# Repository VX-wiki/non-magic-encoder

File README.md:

# Non-Magic Encoder

> ### ⚠️ Read this first: do you actually need one?
>
> **The stock Broadcom optical encoder is magically good when it works.** It is accurate, clean, and there is genuinely nothing wrong with it. Its *only* real weakness is that it is **mechanically fragile**: a delicate optical disc, optics, and aging plastic living in a hot, vibrating drivetrain. If your optical encoder is healthy, **leave it alone**. Nothing here will beat it.
>
> **Non-Magic has no magical properties.** Per the comparison report it does an essentially **identical job**: same current per torque, same heat, same efficiency. It will **not** make your scooter faster, more efficient, or smoother. Treat any apparent "improvement" as noise until proven otherwise.
>
> **This is still hardware under active test.** Non-Magic R1 is community beta with limited hours on a single bike. A lot can still go wrong: installation, adhesives, alignment, calibration, and long-term durability are all unproven at scale. The *one* thing it is meant to bring, better mechanical robustness from having no fragile optical disc, is **plausible but unproven**, and only earns that title after years of real-world service. The only honest reason to fit one today is that your optical encoder has already failed, or you are deliberately experimenting and accept the risk.

## Status and scope

Non-Magic R1 is **community-beta DIY hardware that is still actively under test.**

It has been bench-tested and road-tested on the author's single Vectrix VX-1 and, in those limited conditions, has shown no measurable power, efficiency, current, or heat penalty versus the OEM optical encoder. That is the *whole* of the evidence so far: one bike, a modest number of hours, one rider. It is a small-batch maker project, not a mass-produced, durability-qualified, or independently certified vehicle component.

**Expect problems.** Installation, calibration, adhesives, alignment, and long-term durability are all places where it can and may go wrong. The headline claim of better *mechanical robustness* over the optical encoder is plausible but **not yet proven**. It only earns that title after surviving years of heat, vibration, and moisture in service. Until then, assume Non-Magic is, at best, an *equal* to a working optical encoder, with robustness as an unproven bet.

Use it only if you understand the installation, calibration, and testing procedure, and only if you are comfortable being part of that test.

## What is this?

Non-Magic is a calibrated magnetic replacement encoder for the Vectrix VX-1 motor: a practical, mechanically robust drop-in for when the fragile stock optical encoder finally fails.

**Why "Non-Magic"?** There is a lot of magic out there: black-box encoders locked to one motor controller, with proprietary firmware you cannot read, repair, or replace. This is a *non-magical* encoder. It is open hardware you can modify, build, and experiment with as you please.

**Works with any stock motor controller firmware.** Non-Magic fully emulates the original optical encoder's parameters, with line-driver outputs matched to the original. There is nothing to reflash on the controller and no firmware lock-in. It drops in and behaves like the factory encoder. The goal is to **match** the optical encoder from a more mechanically robust platform, not to beat it.

A good encoder matters because the motor controller has to know rotor position before it can switch the windings cleanly. A weak or misaligned encoder can still make the wheel turn, but it can also add current ripple, heat, whine, rough commutation, lower efficiency, and extra stress on the inverter capacitors. The encoder is a small part, but it decides how cleanly the whole motor system works.

The comparison report now covers **two tests**, both against the factory optical encoder on the same stock controller firmware:

- **Bench (no-load).** On the stand, Non-Magic held its own on power and produced a slightly cleaner commutation signature through the main test band, with more sharply defined motor switching, run for run.
- **Road (loaded).** Ridden on public road under real load up to ~110 A, the two encoders were **indistinguishable**: same current for the same torque (within ~1%), the same heat in the inverter and DC-link capacitors, the same cruise/touring consumption (whole-ride energy 689 vs 690 Wh), and the same regen behaviour. The road test closes the bench's main open question: loaded efficiency and component heating.

The honest bottom line: across both tests the calibrated Non-Magic encoder performs **at least as well** as the OEM optical encoder, with no measurable power, efficiency, or heat penalty. "At least as well" is the ceiling of the claim, not a promise of better, and it still rests on a single bike over limited hours. Read the full comparison report here:

[Non-Magic encoder comparison report (rev2: bench + road)](assets/docs/Non-Magic-encoder-comparison-report-rev2-270626.pdf)

## Specifications

| | |
| --- | --- |
| Sensing IC | MT6835, 21-bit high-accuracy magnetic angle encoder |
| Core resolution | 21-bit |
| Accuracy | User auto-calibration with distortion compensation, target INL < ±0.07° |
| Max rotation speed | Up to 120,000 RPM |
| Operating temperature | −40 to +125 °C |
| Output drivers | AM26C31QDR automotive line drivers |
| Output interface | Connections match the original optical encoder |
| Controller firmware | Works with any stock motor controller firmware. Fully emulates the original encoder's parameters, no reflash, no lock-in |
| Mounting | Robust mechanical mount, designed for a hot, vibrating drivetrain |

## Buy DIY Kit

<p align="center">
  
  <br>
  <sub>self installation required · community-beta, install at your own risk</sub>
</p>

<p align="center">
  <strong>Proceeds support a non-profit makerspace in Riga, Latvia.</strong><br>
  <sub>The first R1 batch is personally funded by the maintainer; Stripe proceeds after payment processing fees go to the makerspace.</sub>
</p>

> ⚠️ **DIY community-beta kit: read before buying or building.**
>
> This is a limited R1 DIY repair/experimenter kit for experienced Vectrix VX-1 owners. It is **not** a plug-and-play consumer accessory: not type-approved, not independently safety-certified, and not supplied as a certified road-use safety component.
>
> Installation requires correct mechanical fitment, magnet alignment, adhesive use, wiring, encoder self-calibration, and motor-controller offset calibration. Incorrect installation or calibration can cause rough commutation, loss of propulsion, overheating, motor or controller damage, or unsafe vehicle behaviour.
>
> Buy only if you can install, inspect, calibrate, and test it yourself. Start with the wheel lifted, test gently, and stop using it immediately if you hear abnormal noise, feel rough running, see faults, or notice unusual heat.
>
> Nothing here limits any mandatory rights or remedies that cannot legally be excluded.

Every board is **tested, programmed, and conformal coated** before it ships. The kit includes **all required parts except threadlocker and adhesive** (listed as consumables below).

## PCB

## How to Install and Use

> ⚠️ **Safety first: read before you touch anything.**
>
> - **Always on the centre stand.** Every calibration and test step below is done with the bike on its centre stand and the **driven (rear) wheel off the ground and free to spin**. The motor can spin that wheel on its own during offset calibration, so never do this with the wheel able to drive the bike.
> - **High voltage.** The Vectrix runs on high-voltage traction electronics. Treat the battery, controller, and wiring as live and dangerous at all times, and take every sane high-voltage precaution whenever you work on the bike.

Installation walkthrough video:

https://github.com/user-attachments/assets/6c1a84cd-9490-44e6-9311-1ca9467ff3d4

A key advantage of Non-Magic is that it **self-calibrates once installed**. The on-board MT6835 builds its own angle-error correction map while the rotor turns slowly. You just spin the rear wheel at roughly 5 km/h with a hand drill pressed against the tyre and hold the calibration button. No special rig, no PC required for this step.

### 1. Mechanical installation

1. **Remove the original encoder assembly.**
2. **Clean the area thoroughly.** No dust, grease, oil, or other contaminants may remain in the motor encoder cavity. A clean, dry surface is critical for both the adhesive bond and the magnetic reading.
3. **Install the magnet holder.** Apply adhesive and push the magnet holder on until the motor shaft bottoms out inside it. Watch the slot in the shaft and the magnet holder; they must align cleanly. Allow the adhesive to set if possible.
4. **Attach the encoder assembly to the motor case.** Use threadlocker on the bolts. Fit each bolt with a wide washer and a serrated washer. **Do not overtighten.**
5. **Connect the encoder connector.**

There are **two separate calibrations**, and they must not be confused:

- **Encoder ASIC self-calibration** (Section 2) calibrates the **encoder**. It runs on the encoder's own MT6835 chip and corrects the magnetic sensor's per-revolution angle-error map, using the **encoder's calibration button and LED**.
- **Motor offset calibration** (Section 3) calibrates the **inverter**. It runs on the Vectrix motor controller, either in diagnostic software or via the throttle/brake/ignition "combo", and teaches the controller the fixed angle between encoder zero and the rotor's magnetic zero.

Do both, in this order. They are different procedures on different hardware; the encoder button does not trigger the controller offset cal, and the controller combo does not trigger the ASIC self-cal.

### 2. Encoder ASIC self-calibration (on the encoder)

1. **Power on the bike, but do not try to start it.**
2. **Turn the wheel by hand and watch the LED.** It should give **5 pulses per wheel revolution**. If it does, the magnet and alignment are good.
3. **Run the calibration spin.** Put the bike on the centre stand and spin the rear wheel with a hand drill pressed against the tyre, holding roughly **5 km/h** (read off the dash or scooter diagnostic software).
4. **Hold the calibration button.** Calibration needs **more than 64 rotations** to complete; expect to hold the button for under ~20 seconds. **THE SPEED TARGET IS APPROX 10-30-ish km/h, so no need to be very precise. If you are too slow or fast- it will just fail and let you know with the led** The LED shows progress:

   | LED state | Meaning |
   | --- | --- |
   | Half brightness | Calibration in progress |
   | Dim | Calibration failed |
   | Full on | Calibration succeeded |

5. **Turn the bike fully off** once calibration succeeds.

### 3. Motor offset calibration (on the inverter)

After the on-board self-cal, the motor controller still needs its own encoder-offset calibration.

**With the Vectrix diagnostics software:** turn the bike on and run the encoder calibration from the diagnostic application. Note this needs a **PeakCAN cable** to talk to the controller. If you don't have one, you can't use the software, so use the combo procedure below instead.

**Without software, the built-in combo procedure:** the controller has a hidden calibration mode you trigger straight from the bars, no cable or software required. (This is the same throttle/brake/ignition combo Vectrix documented for the original optical encoder; it works identically here.)

1. Put the bike on its **centre stand** and confirm the rear wheel is off the ground, free to spin, and the bike is stable.
2. Fold up the side-stand / kickstand.
3. Make sure the ignition key is in the **OFF** position.
4. Press the kill switch to the **RUN** position.
5. Turn the throttle **fully open** and squeeze the **left brake** lever, and hold both.
6. While still holding throttle and brake, turn the ignition **ON**.
7. Keep holding until the dashboard activates and the **WRENCH** icon / tell-tale light stays on, then release the throttle and brake.
8. Calibration starts automatically: the wheel begins to rotate and the speedometer needle sweeps from 0 km/h up to 120 km/h and back to zero.
9. After a few seconds the **WRENCH** icon disappears. Calibration is done.
10. If the process repeats itself over and over, the encoder cannot find a valid calibration; it requires inspection, cleaning, or replacement.

> **Caution:** the bike is still in GO mode during and after this procedure. Turning the throttle will activate the motor.

Then test gently first, listening for rough commutation or abnormal motor/controller heat.

> **Note: check your phase wiring.** The author's bike came equipped with a "magic" commercial magnetic encoder as purchased, and its motor phase wires were connected A-B, B-C, C-A. Neither the optical nor the magnetic encoder would work until the phases were swapped back to their respective factory positions: A-A, B-B, C-C. If the motor refuses to run or commutates badly regardless of encoder calibration, verify the phase wiring is in its correct factory order before troubleshooting the encoder further.

Installation consumables:

| No | Name | Qty | Notes | Link |
| ---: | --- | ---: | --- | --- |
| 1 | Threadlocker, blue or red | as needed | For encoder holder to motor case | commodity |
| 2 | Magnet holder to motor adhesive | as needed | Preferred order: automotive gasket maker, toughened cyanoacrylate, two-part epoxy, threadlocker | commodity |

## Make Your Own

Or make your own. The full design sources are below.

> ⚠️ **License first.** These files are released under **CC BY-NC-SA 4.0**. You may build, modify, and share them, but you may **not sell them or profit in any way**, and any derivative must stay under the same license. See [License](#license). No magic, no freeloading.

**Total cost is roughly €25–60 per unit**, depending on how you scale and source the parts and what tools and materials you already have on hand.

The DIN fasteners are standard commodity parts; source them from any supplier by their DIN number.

| No | Name | Image | Qty | Notes | Link |
| ---: | --- | :---: | ---: | --- | --- |
| 1 | Main PCB |  | 1 | Gerbers + assembly files | [production archive](hardware/kicad/production/non-magic-encoder-r1.zip) |
| 2 | Printed PCB holder* |  | 1 | FDM PA6-GF, PA6-CF, PPS-CF, or MFJ PA12-GB. IMPORTANT! | [STL](hardware/printed-parts/encoder-printed-holder-r1.STL) |
| 3 | Printed magnet holder* |  | 1 | FDM PA6-GF, PA6-CF, PPS-CF, or MFJ PA12-GB. IMPORTANT! | [STL](hardware/printed-parts/magnet-holder-r1.STL) |
| 4 | 3M DP8910NS adhesive | | 0.1 g | Bonds the magnet to the printed nylon holder. Alternate adhesive can be used, but it is risky; see note below | [3M](https://www.3m.com/) |
| 5 | 10x5 neodymium magnet |  | 1 | N45 or better, diametrically magnetized | commodity |
| 6 | Sleeve DIN 7340 | | 4 | Cu, 2.6 x 5 x 3 | commodity |
| 7 | Washer DIN 9021 | | 4 | M2.5, OD8 | commodity |
| 8 | Washer DIN 6798 Type A | | 4 | M2.5 | commodity |
| 9 | Bolt DIN 7985 | | 4 | M2.5, length to suit installation | commodity |
| 10 | Screw DIN 7981 ST 2.0 x 6 | | 4 | EJOT PT is better | commodity |
| 11 | Conformal coating | | as needed | Weatherproof the populated PCB; see note below | commodity |

*The encoder lives in a harsh environment. You must use glass-filled high-performance material for the encoder support. PA6-GF is used in the current units. Standard SLS PA12 or PA11 may not be up to the task.

**Why the 3M DP8910NS adhesive matters:** nylon (PA6 through PA12) is a *low surface energy* plastic, so most common adhesives will not key into it and the bond fails. DP8910NS is formulated specifically for low-energy substrates like nylon and polypropylene, which is why it is the recommended choice for bonding the magnet to the printed holder. Substituting a general-purpose adhesive is the most likely way to end up with magnet delamination.

**Conformal coating is important.** The encoder lives in a harsh place: heat, vibration, moisture, and contamination. Conformal coating the populated PCB is essential weatherproofing that protects against corrosion and conductive dirt. Factory-built kits ship already coated; if you build your own, do not skip this step.

### Design files

Everything needed to fabricate, assemble, or modify the board:

| File | Description |
| --- | --- |
| [Schematic (PDF)](hardware/non-magic-encoder-r1-schematic.pdf) | R1 schematic |
| [Production archive (ZIP)](hardware/kicad/production/non-magic-encoder-r1.zip) | Gerbers, BOM, and pick-and-place for fabrication |
| [KiCad project](hardware/kicad/) | Editable sources (`.kicad_pro`, `.kicad_sch`, `.kicad_pcb`), libraries, and footprints |
| [Board STEP model](hardware/encoder-pcb-r1.step) | 3D model of the assembled PCB |
| [PCB holder STL](hardware/printed-parts/encoder-printed-holder-r1.STL) | Printed encoder support (glass-filled material, see note above) |
| [Magnet holder STL](hardware/printed-parts/magnet-holder-r1.STL) | Printed magnet carrier (glass-filled material, see note above) |
| [MT6835 datasheet](hardware/kicad/docs/MT6835_Rev.1.3.pdf) | Sensing IC reference |

## Informal Risk Assessment

A short FMEA-style note on the failure modes that actually matter on this hardware. This is not an ISO 26262 compliance claim, safety case, or certification. Severity, likelihood, and controllability are qualitative.

| Failure mode | Cause | Effect | Severity | Risk reduction |
| --- | --- | --- | --- | --- |
| Bad commutation | Magnet misalignment or skipped auto-calibration | Motor switches at the wrong angle, drawing excess current and overheating the motor and controller | Medium-High | Verify magnet centering and air gap, run the auto-calibration before riding, test first with the wheel lifted and watch for abnormal heat |
| Loss of board power | Cracked or shorted MLCC on the PCB shorts the supply and trips the upstream resettable fuse | Encoder goes dead, controller loses position, **motor coasts to a halt** (no torque, not a runaway) | Medium | Use quality MLCCs, avoid board flex during assembly and mounting, handle the populated PCB carefully |
| Mechanical failure | Magnet delamination: the magnet's adhesive bond to its holder lets go | Position signal is lost or wrong, propulsion drops out | Medium | Use the ranked adhesives with proper surface prep, use only glass-filled holder material, inspect after the first heat cycles |

Before riding: confirm the magnet is centred, run auto-calibration, and do the first run with the driven wheel lifted and a safe way to cut power. Treat any suspected encoder fault as stop-use until inspected. Road or public-use suitability is outside the scope of this project.

## Getting help

Two ways to get help or report a problem:

- **Open an issue.** [Create an issue in this repo](../../issues/new) for bugs, broken links, install trouble, or questions. This is the best place for anything others might hit too.
- **Chat with the community.** Reach out on WhatsApp in the **Open Source Magic Encoder** group, part of the wider **Vectrix Worldwide** community. It's the fastest way to get hands-on install and calibration help from other owners.

## Contributing

Contributions are welcome. Fork the repo, make your changes, and open an issue or pull request:

- **Found a bug or have an idea?** Open an issue first so it can be discussed.
- **Improved the hardware, holders, or docs?** Fork it, commit your changes, and open a pull request from your fork.

Anything you contribute is released under the same **CC BY-NC-SA 4.0** license as the rest of the project (see below), so improvements stay open for everyone.

## License

This project is licensed under the Creative Commons Attribution-NonCommercial-ShareAlike 4.0 International license (CC BY-NC-SA 4.0). See [LICENSE](LICENSE).

In plain terms:

- **Attribution.** You may use, build, and adapt this design, as long as you credit the project.
- **NonCommercial.** You may **not** sell these encoders or profit from them in any way. This is deliberate: the kits exist to fund a non-profit makerspace, not to seed a competing product.
- **ShareAlike.** If you modify and share the design, you must release your version under the same license, so improvements stay open for everyone.

**A simple test for what's allowed:** if you can order, say, 5–10 units from China and give them away to friends or others *at cost*, making no profit, taking no salary, charging nothing beyond what the parts and fabrication actually cost you, then the answer is **yes, that's fine**. The moment you mark them up, pay yourself, or otherwise come out ahead, it stops being NonCommercial and is no longer permitted.

This keeps the encoder in the spirit of the name: open to modify, build, and experiment with, but never to lock up or sell.

## Disclaimer

No warranties are provided. This is experimental hardware intended for off-road, testing, research, and maker use only. It is not certified as a road-use safety component.

Build, install, calibrate, and use it entirely at your own risk. You are responsible for checking fitment, alignment, wiring, calibration, local legality, and safe operation. The authors and contributors are not responsible for damage, injury, loss, or any other consequences from making, installing, modifying, or using this encoder.

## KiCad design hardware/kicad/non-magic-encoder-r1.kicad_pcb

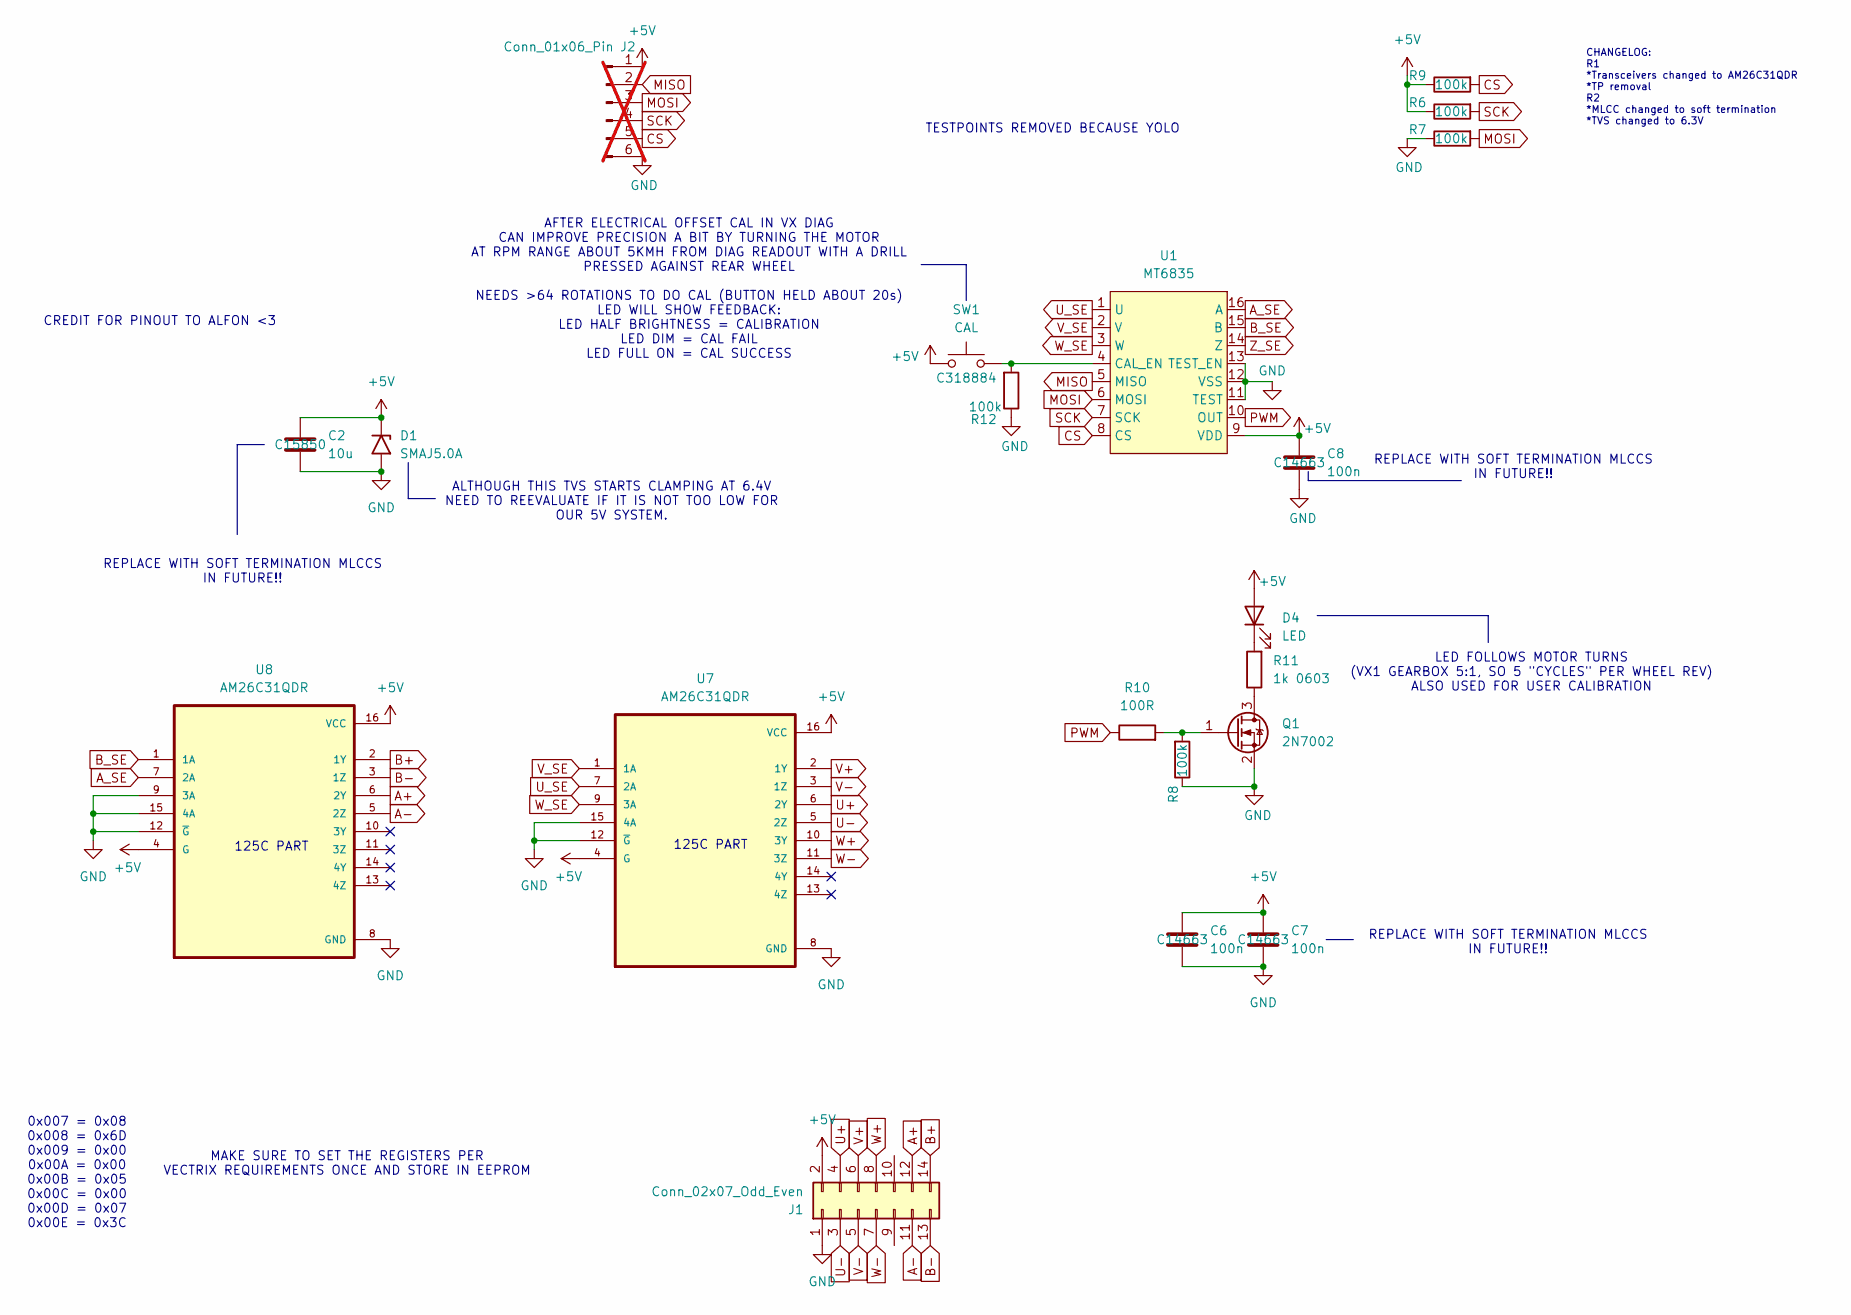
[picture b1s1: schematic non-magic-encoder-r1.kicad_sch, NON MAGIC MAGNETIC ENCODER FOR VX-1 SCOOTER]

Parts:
C2: 10u; C_0805_2012Metric; LCSC C15850
C6, C7, C8: 100n; C_0603_1608Metric; LCSC C14663
D1: SMAJ5.0A; D_SMA; LCSC C5189780
D4: LED; LED_D3.0mm_Clear
J1: Conn_02x07_Odd_Even; CONN-TH_14P-P3.00_HC-MX3.0-2X7AW; LCSC C3294388
J2: Conn_01x06_Pin; PinHeader_1x06_P2.54mm_Vertical; not fitted
Q1: 2N7002; SOT-23; LCSC C8545
R6, R7, R8, R9, R12: 100k; R_0603_1608Metric; LCSC C25803
R10: 100R; R_0603_1608Metric; LCSC C4177
R11: 1k 0603; R_0603_1608Metric; LCSC C21190
SW1: CAL; SW-SMD_4P-L5.1-W5.1-P3.70-LS6.5-TL_H1.5; LCSC C318884
U1: MT6835; TSSOP-16_4.4x5mm_P0.65mm; LCSC C2932578
U7, U8: AM26C31QDR; SOIC127P600X175-16N; LCSC C337769

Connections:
+5V: C2.1, C6.1, C7.1, C8.1, D1.1 (A1), D4.2 (A), J1.2, J2.1, R6.1, R9.1, SW1.1, U1.9 (VDD), U7.4 (G), U7.16 (VCC), U8.4 (G), U8.16 (VCC)
A+: J1.12, U8.6 (2Y)
A-: J1.11, U8.5 (2Z)
A_SE: U1.16 (A), U8.7 (2A)
B+: J1.14, U8.2 (1Y)
B-: J1.13, U8.3 (1Z)
B_SE: U1.15 (B), U8.1 (1A)
CS: J2.5, R9.2, U1.8 (CS)
GND: C2.2, C6.2, C7.2, C8.2, D1.2 (A2), J1.1, J2.6, Q1.2 (S), R7.1, R8.1, R12.1, U1.11 (TEST), U1.12 (VSS), U1.13 (TEST_EN), U7.8 (GND), U7.12 (~G), U7.15 (4A), U8.8 (GND), U8.9 (3A), U8.12 (~G), U8.15 (4A)
MISO: J2.2, U1.5 (MISO)
MOSI: J2.3, R7.2, U1.6 (MOSI)
unnamed: D4.1 (K), R11.2
unnamed: Q1.3 (D), R11.1
unnamed: Q1.1 (G), R8.2, R10.2
unnamed: R12.2, SW1.2, U1.4 (CAL_EN)
PWM: R10.1, U1.10 (OUT)
SCK: J2.4, R6.2, U1.7 (SCK)
U+: J1.4, U7.6 (2Y)
U-: J1.3, U7.5 (2Z)
U_SE: U1.1 (U), U7.7 (2A)
V+: J1.6, U7.2 (1Y)
V-: J1.5, U7.3 (1Z)
V_SE: U1.2 (V), U7.1 (1A)
W+: J1.8, U7.10 (3Y)
W-: J1.7, U7.11 (3Z)
W_SE: U1.3 (W), U7.9 (3A)
Z_SE: U1.14 (Z)

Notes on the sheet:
REPLACE WITH SOFT TERMINATION MLCCS IN FUTURE!!
MAKE SURE TO SET THE REGISTERS PER VECTRIX REQUIREMENTS ONCE AND STORE IN EEPROM
CREDIT FOR PINOUT TO ALFON <3
LED FOLLOWS MOTOR TURNS (VX1 GEARBOX 5:1, SO 5 "CYCLES" PER WHEEL REV) ALSO USED FOR USER CALIBRATION
0x007 = 0x08 0x008 = 0x6D 0x009 = 0x00 0x00A = 0x00 0x00B = 0x05 0x00C = 0x00 0x00D = 0x07 0x00E = 0x3C
125C PART
CHANGELOG: R1 *Transceivers changed to AM26C31QDR *TP removal R2 *MLCC changed to soft termination *TVS changed to 6.3V
TESTPOINTS REMOVED BECAUSE YOLO
ALTHOUGH THIS TVS STARTS CLAMPING AT 6.4V NEED TO REEVALUATE IF IT IS NOT TOO LOW FOR OUR 5V SYSTEM.
AFTER ELECTRICAL OFFSET CAL IN VX DIAG CAN IMPROVE PRECISION A BIT BY TURNING THE MOTOR AT RPM RANGE ABOUT 5KMH FROM DIAG READOUT WITH A DRILL PRESSED AGAINST REAR WHEEL NEEDS >64 ROTATIONS TO DO CAL (BUTTON HELD ABOUT 20s) LED WILL SHOW FEEDBACK: LED HALF BRIGHTNESS = CALIBRATION LED DIM = CAL FAI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

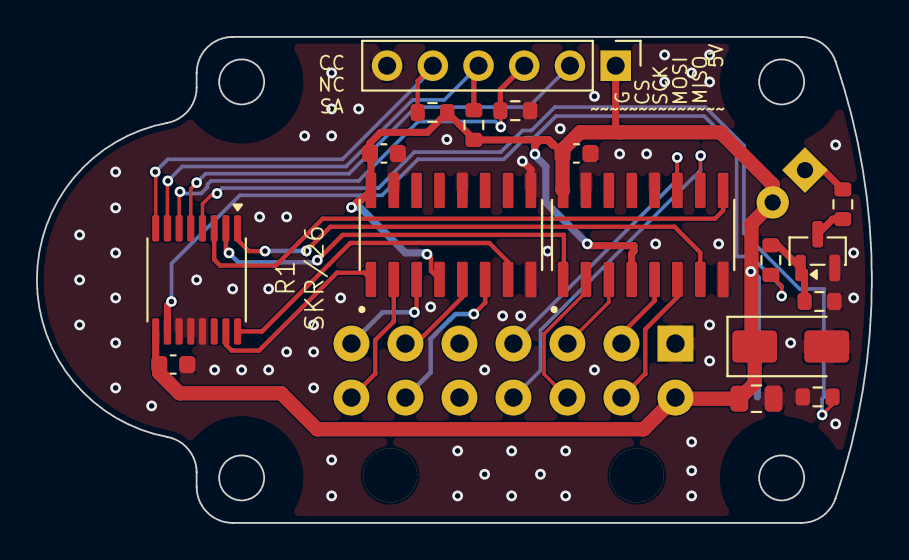
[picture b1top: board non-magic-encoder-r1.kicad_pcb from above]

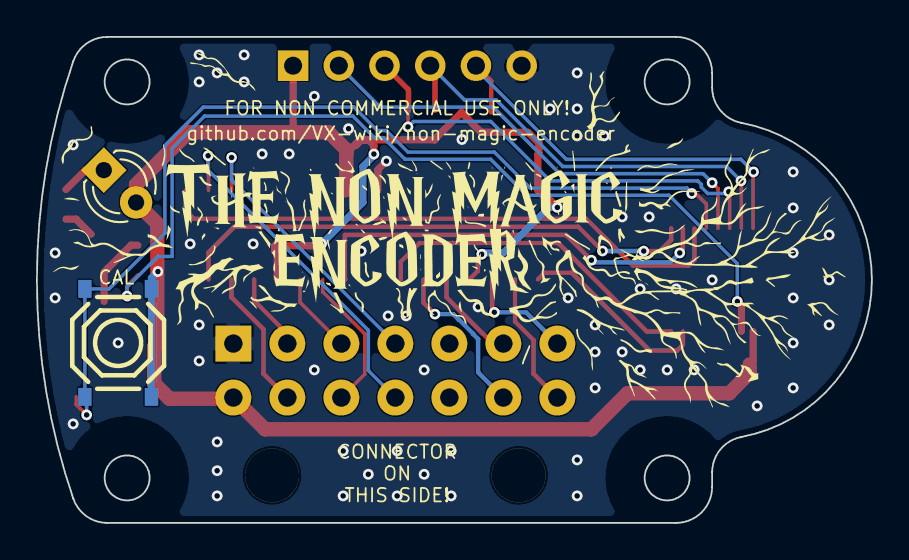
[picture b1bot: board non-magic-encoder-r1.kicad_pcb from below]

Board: 2 copper layers, 46.4 x 27.0 mm, 20 parts (3 on the bottom side), 26 nets.

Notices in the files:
hardware/kicad/non-magic-encoder-r1.kicad_pcb:
LICENCE: CC-NC-SA
